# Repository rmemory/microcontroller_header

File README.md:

The purpose of this project is to design a hardware (PCB) header which can be used as an interface from general I/O hardware to any uC of choice.

For example, lets say we wish to measure something (voltage, current, etc). It allows us to use any micro controller (teensy, arduino, beaglebone, etc) to interface to the measurement.

Here is the pin out. Note that it is "keyed" meaning, its designed such that the connector cannot be used with the wrong polarity.

The first usage of the header will be to integrate it with the Teensy 3.2: https://www.pjrc.com/store/teensy32.html

The microcontroller header will be used as an interface to a sensor board.

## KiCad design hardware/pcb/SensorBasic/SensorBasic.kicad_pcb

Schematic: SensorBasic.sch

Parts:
C1, C2, C3: .1; C_0805_HandSoldering; MPN C0805C104K5RACTU
D1, D2, D3, D4, D5, D6, D7, D8: LED; LED_0805; MPN SML-LXR85IC-TR
R1, R2, R3, R4, R5, R6, R7, R8, R9, R10, R12, R13, R14, R15: R; R_0805_HandSoldering
R11: Photo Resistor; CP_Radial_Tantal_D5.5mm_P5.00mm; MPN PDV-P8103-ND
U1: MicroC_Header; MicroC_Header_Pitch2.54mm
U2: DS7505; SOIC-8_3.9x4.9mm_Pitch1.27mm; MPN DS7505S+-ND
U3: 74HC595-PWR; SOIC-16_3.9x9.9mm_Pitch1.27mm; MPN 74HC595D,118

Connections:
/3.3V: C2.2, C3.2, R1.1, U1.12 (PWR_CORE), U2.8 (VDD), U3.10, U3.16
/5V: R10.1, U1.1 (PWR_IO)
/OS: R1.2, U1.4 (SPI_MISO/GPIO_1), U2.3 (OS)
/PR_BOT: R11.2, R12.1, U1.16 (AIO_1/GPIO_9)
/PR_TOP: R10.2, R11.1, U1.15 (AIO_0/GPIO_8)
/SCL: U1.13 (I2C_SCLK_GPIO_6), U2.2 (SCL)
/SDA: U1.14 (I2C_SDAT/GPIO_7), U2.1 (SDA)
/clockPin: U1.5 (SPI_CLK/GPIO_2), U3.11
/dataPin: U1.6 (SPI_CS/GPIO_3), U3.14
/latchPin: C1.1, U1.7 (USART_RX/GPIO_4), U3.12
GND: C1.2, C2.1, C3.1, R2.2, R3.2, R4.2, R5.2, R6.2, R7.2, R8.2, R9.2, R12.2, R13.2, R14.2, R15.2, U1.10 (GND), U1.19 (GND), U2.4 (GND), U3.8, U3.13
unnamed: D1.1 (K), R5.1
unnamed: D1.2 (A), U3.7
unnamed: D2.1 (K), R6.1
unnamed: D2.2 (A), U3.6
unnamed: D3.1 (K), R7.1
unnamed: D3.2 (A), U3.5
unnamed: D4.1 (K), R8.1
unnamed: D4.2 (A), U3.4
unnamed: D5.1 (K), R9.1
unnamed: D5.2 (A), U3.3
unnamed: D6.1 (K), R13.1
unnamed: D6.2 (A), U3.2
unnamed: D7.1 (K), R14.1
unnamed: D7.2 (A), U3.1
unnamed: D8.1 (K), R15.1
unnamed: D8.2 (A), U3.15
unnamed: R2.1, U2.5 (A2)
unnamed: R3.1, U2.6 (A1)
unnamed: R4.1, U2.7 (A0)

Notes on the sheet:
Analog Sensor (Resistive)
I2C Temp Sensor

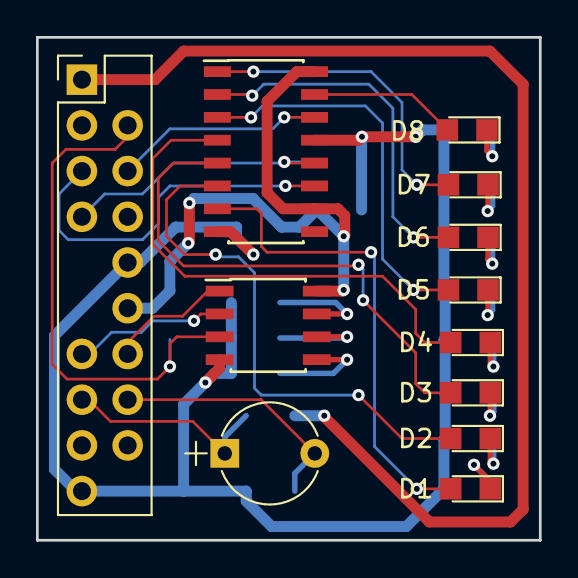
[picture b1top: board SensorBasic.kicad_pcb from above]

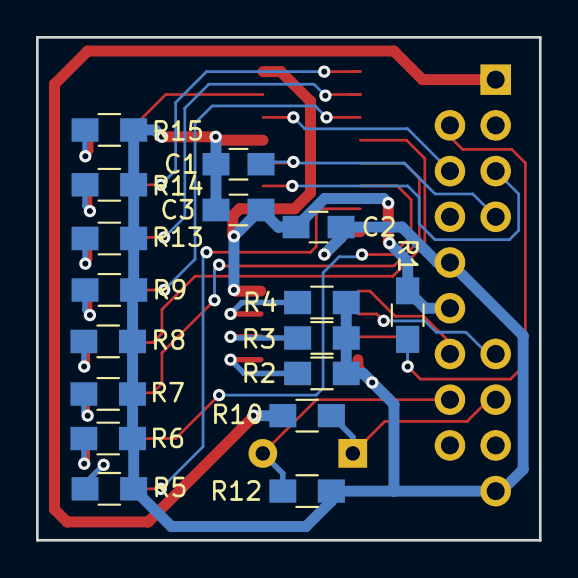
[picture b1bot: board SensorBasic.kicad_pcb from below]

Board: 2 copper layers, 27.9 x 27.9 mm, 29 parts (17 on the bottom side), 30 nets.

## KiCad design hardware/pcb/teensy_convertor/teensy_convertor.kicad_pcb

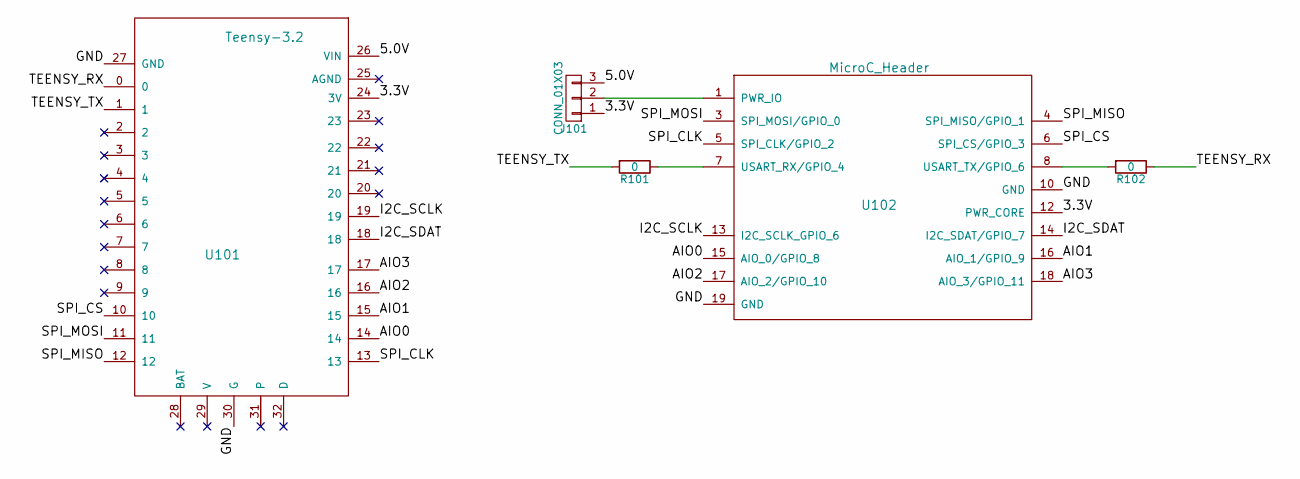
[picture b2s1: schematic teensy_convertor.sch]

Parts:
J101: CONN_01X03; Pin_Header_Straight_1x03_Pitch2.54mm
R101, R102: 0; R_0805_HandSoldering
U101: Teensy-3.2; Teensy-32
U102: MicroC_Header; MicroC_Header_Pitch2.54mm

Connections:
/3.3V: J101.1, U101.24 (3V), U102.12 (PWR_CORE)
/5.0V: J101.3, U101.26 (VIN)
/AIO0: U101.14, U102.15 (AIO_0/GPIO_8)
/AIO1: U101.15, U102.16 (AIO_1/GPIO_9)
/AIO2: U101.16, U102.17 (AIO_2/GPIO_10)
/AIO3: U101.17, U102.18 (AIO_3/GPIO_11)
/GND: U101.27 (GND), U101.30 (G), U102.10 (GND), U102.19 (GND)
/I2C_SCLK: U101.19, U102.13 (I2C_SCLK_GPIO_6)
/I2C_SDAT: U101.18, U102.14 (I2C_SDAT/GPIO_7)
/SPI_CLK: U101.13, U102.5 (SPI_CLK/GPIO_2)
/SPI_CS: U101.10, U102.6 (SPI_CS/GPIO_3)
/SPI_MISO: U101.12, U102.4 (SPI_MISO/GPIO_1)
/SPI_MOSI: U101.11, U102.3 (SPI_MOSI/GPIO_0)
/TEENSY_RX: R102.1, U101.0
/TEENSY_TX: R101.2, U101.1
unnamed: J101.2, U102.1 (PWR_IO)
unnamed: R101.1, U102.7 (USART_RX/GPIO_4)
unnamed: R102.2, U102.8 (USART_TX/GPIO_6)

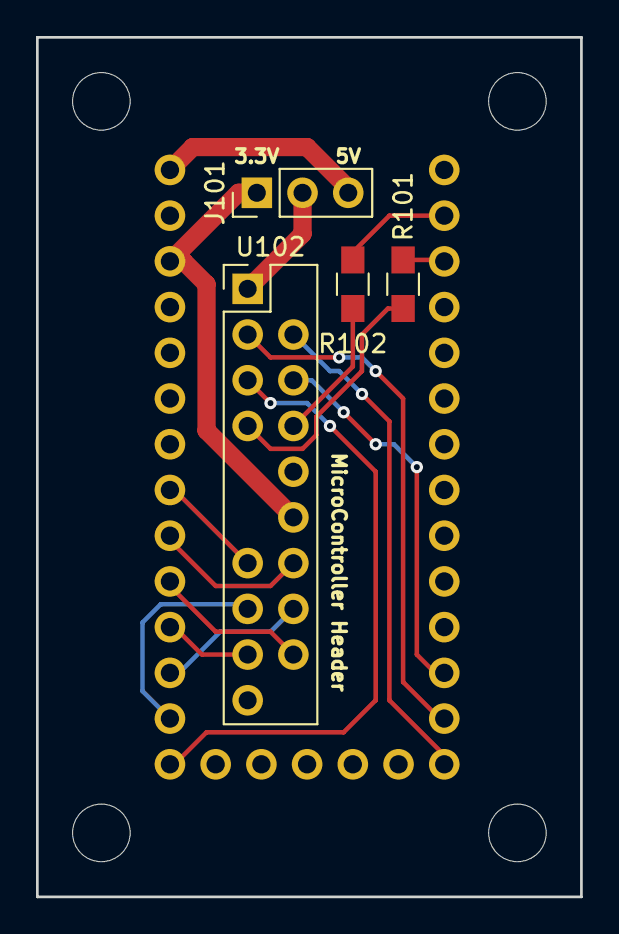
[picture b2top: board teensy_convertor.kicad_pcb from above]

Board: 2 copper layers, 30.2 x 47.8 mm, 5 parts (1 on the bottom side), 18 nets.

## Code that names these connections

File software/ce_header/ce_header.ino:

#define CE_spi_cs_gpio3 10
#define CE_spi_mosi_gpio0 11
#define CE_spi_miso_gpio1 12
#define CE_spi_clk_gpio2 13
#define CE_usart_tx_gpio4 1 // Teensy TX
#define CE_usart_rx_gpio5 0 // Teensy RX
#define CE_i2c_sclk_gpio6 19
#define CE_i2c_sdat_gpio7 18
#define CE_aio0_gpio8 14
#define CE_aio1_gpio9 15
#define CE_aio2_gpio10 16
#define CE_aio3_gpio11 17

/*
  Shift Register Example
 for 74HC595 shift register

 This sketch turns reads serial input and uses it to set the pins
 of a 74HC595 shift register.

 Hardware:
 * 74HC595 shift register attached to pins 8, 12, and 11 of the Arduino,
 as detailed below.
 * LEDs attached to each of the outputs of the shift register.

 Created 22 May 2009
 Created 23 Mar 2010
 by Tom Igoe

 */

/* 
 Latch = Teensy pin 0 == CE Header pin 7 == 74HC595 pin 12
Data clk = Teensy pin 13 = CE Header pin 5 == 74HC595 pin 11
Data = Teensy pin 10 = CD Header pin 6 = 74HC595 pin 14
*/

 #define latchPin CE_usart_tx_gpio4
 #define dataPin CE_spi_cs_gpio3
 #define clockPin CE_spi_clk_gpio2


void setup() {
  //set pins to output because they are addressed in the main loop
  pinMode(latchPin, OUTPUT);
  pinMode(dataPin, OUTPUT);  
  pinMode(clockPin, OUTPUT);
  Serial.begin(9600);
  Serial.println("reset");
}

void loop() {
  if (Serial.available() > 0) {
    // ASCII '0' through '9' characters are
    // represented by the values 48 through 57.
    // so if the user types a number from 0 through 9 in ASCII, 
    // you can subtract 48 to get the actual value:
    int bitToSet = Serial.read() - 48;

  // write to the shift register with the correct bit set high:
    registerWrite(bitToSet, HIGH);
  }
}

// This method sends bits to the shift register:

void registerWrite(int whichPin, int whichState) {
// the bits you want to send
  byte bitsToSend = 0;

  // turn off the output so the pins don't light up
  // while you're shifting bits:
  digitalWrite(latchPin, LOW);

  // turn on the next highest bit in bitsToSend:
  bitWrite(bitsToSend, whichPin, whichState);

  // shift the bits out:
  shiftOut(dataPin, clockPin, MSBFIRST, bitsToSend);

    // turn on the output so the LEDs can light up:
  digitalWrite(latchPin, HIGH);

}

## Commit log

2017-05-16 Initial README
2017-05-16 Adding screenshot to readme
2017-05-17 move image to new images directory
2017-05-17 Add initial kicad project
2017-05-28 rearrange directory structure
2017-05-28 Add lables from Teensy to microcontroller header
2017-05-28 Add a few more notes related to the Teensy 3.2
2017-05-29 Initial association and import into the layout tool
2017-05-29 Initial layout
2017-06-02 First cut of the complete layout with mounting holes
2017-06-04 Minor update to the schematic
2017-06-05 final layout
2017-06-05 Add gerber files, and submit to Oshpark
2017-06-05 add zip file for teensy submission to oshpark, and also created a new blank project for the basic sensor board
2017-06-05 Initial SensorBasic project
2017-06-10 Initial schematic for Sensor
2017-06-11 Add schematics symbol for temperature sensor, DS7505
2017-06-18 Final schematic
2017-06-19 Add footprint association and initial layout
2017-06-19 First layout with initial placements of ICs and LEDs. Still need to place the resistors, capacitors, and route traces
2017-06-20 First iteration of adding traces
2017-06-21 First version of final layout
2017-07-30 Added MPN part numbers to all parts except the resistors
2017-07-30 Add initial gerber and drill files
2017-07-30 add zip file containing gerbers
2017-07-30 final update of pcb file
2017-11-22 code to test operation of 74hc595 shift register
